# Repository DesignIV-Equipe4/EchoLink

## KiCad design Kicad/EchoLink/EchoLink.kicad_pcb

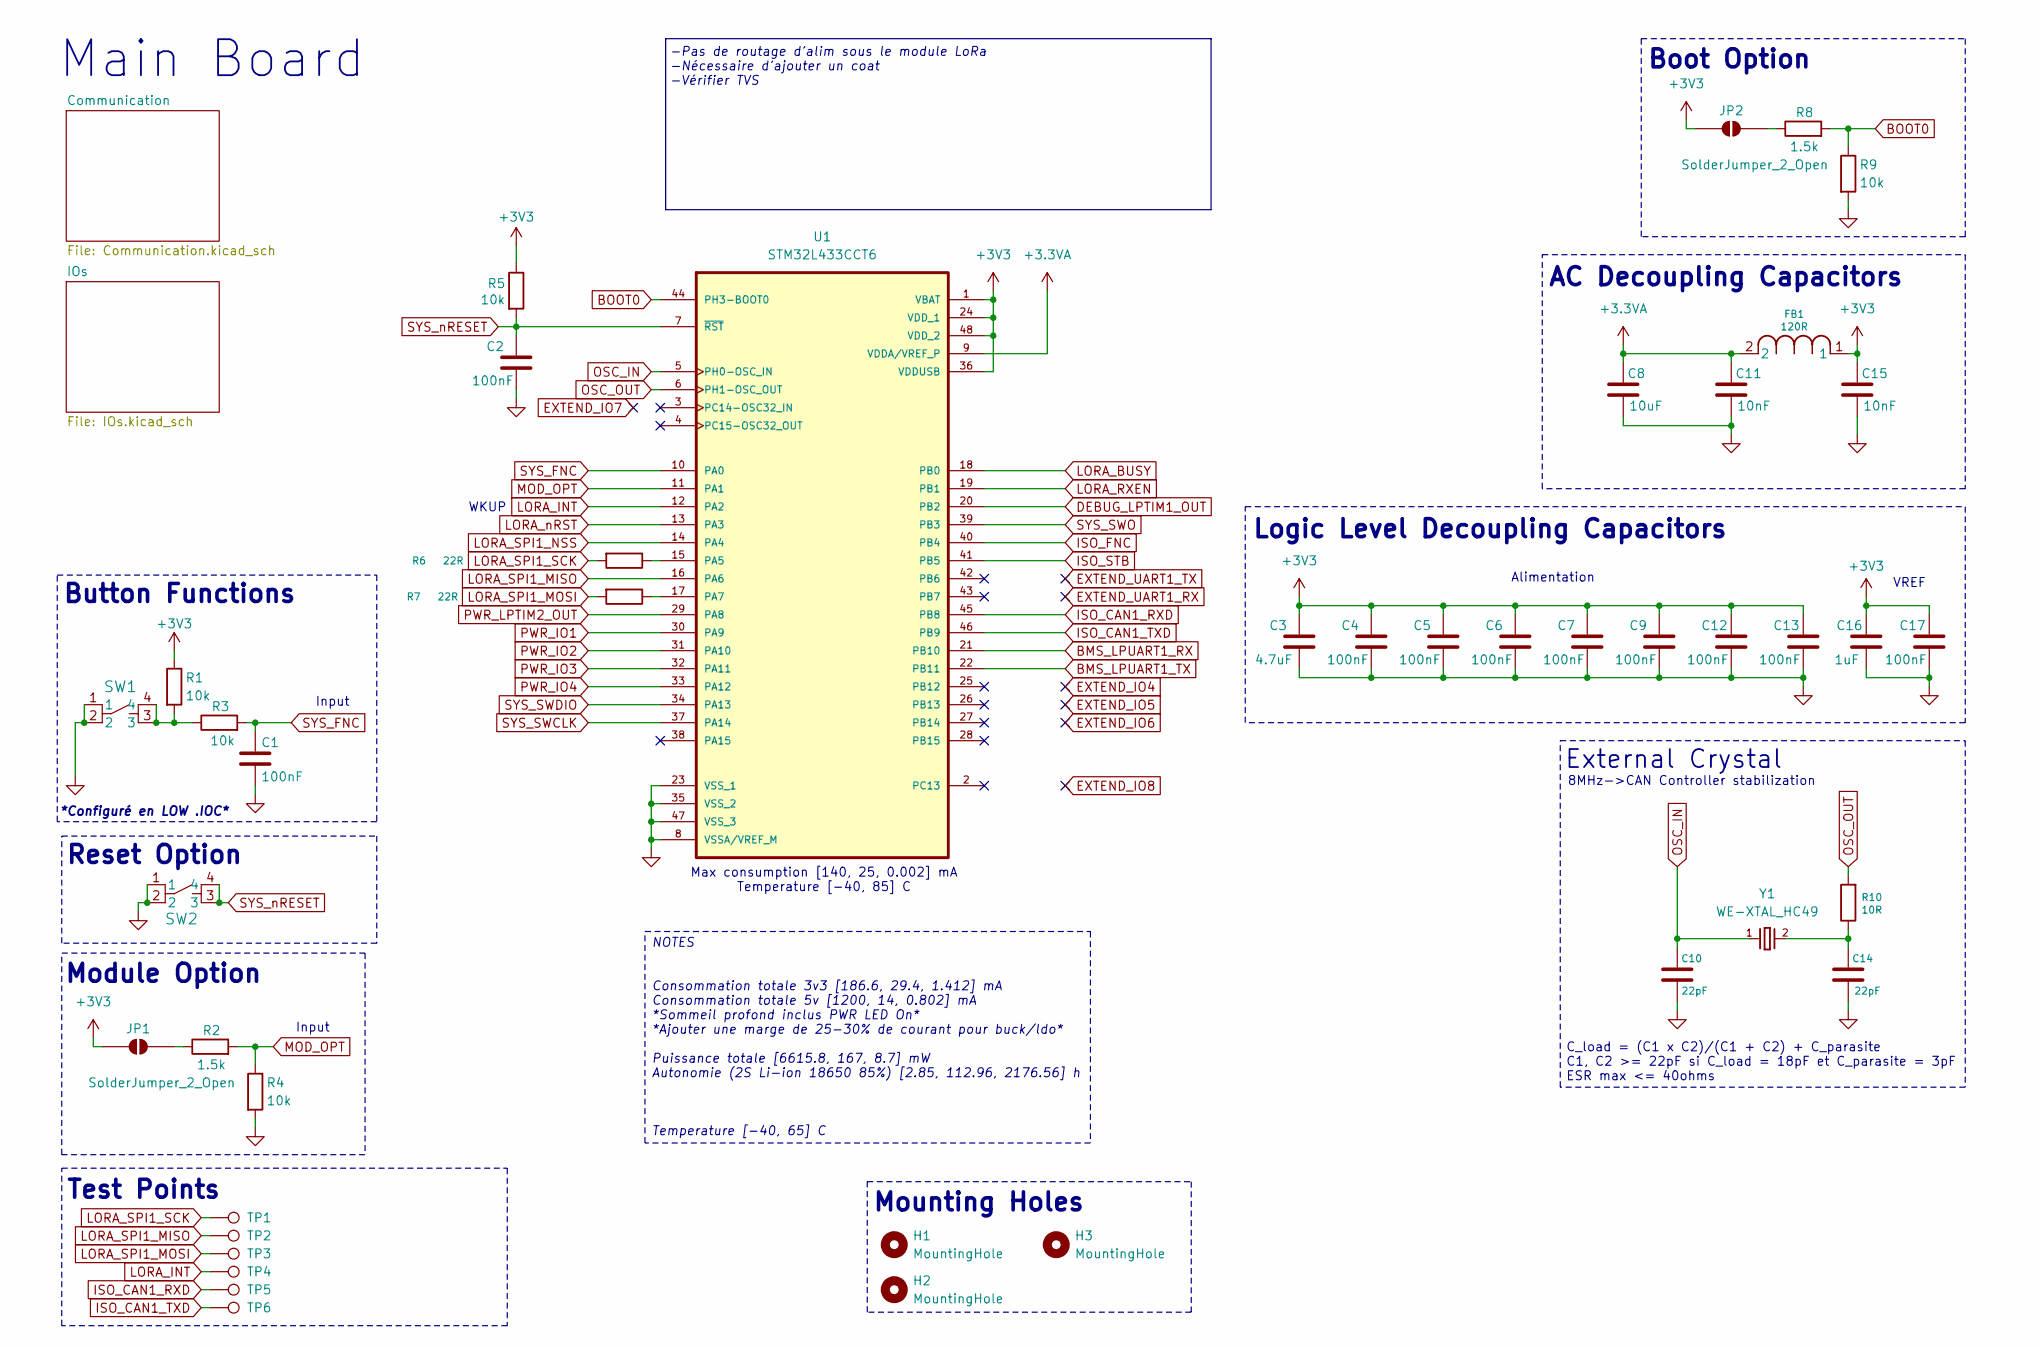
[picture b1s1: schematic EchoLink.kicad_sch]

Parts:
C1, C2, C4, C5, C6, C7, C9, C12, C13, C17: 100nF; C_0603_1608Metric; Manufacturer_Part_Number C0603C104K5RACTU; DigiKey_Part_Number 311-3342-1-ND
C3: 4.7uF; C_0603_1608Metric; Manufacturer_Part_Number GRM188R61E475KE11D; DigiKey_Part_Number 311-3342-1-ND
C8: 10uF; C_0603_1608Metric; Manufacturer_Part_Number LMK107BBJ106MALT; DigiKey_Part_Number 4713-GMC10X5R106M35NTTR-ND
C10, C14: 22pF; C_0402_1005Metric; Manufacturer_Part_Number QSCT251Q220F1GV001E; DigiKey_Part_Number 712-QSCT251Q220F1GV001ECT-ND
C11, C15: 10nF; C_0402_1005Metric; Manufacturer_Part_Number GRM155R71C103KA01D; DigiKey_Part_Number 490-1313-1-ND
C16: 1uF; C_0603_1608Metric; Manufacturer_Part_Number C0603C105K4RACTU; DigiKey_Part_Number 311-3342-1-ND
FB1: 120R; R_0805_2012Metric; Manufacturer_Part_Number 2508051217Y6; DigiKey_Part_Number 1934-1472-1-ND
H1, H2, H3: MountingHole; MountingHole_2.2mm_M2_Pad_Via
JP1, JP2: SolderJumper_2_Open; SolderJumper-2_P1.3mm_Open_RoundedPad1.0x1.5mm
R1, R4, R5, R9: 10k; R_0603_1608Metric; Manufacturer_Part_Number RC0603FR-0710KL; DigiKey_Part_Number 311-10.0KHRCT-ND
R2, R8: 1.5k; R_0603_1608Metric; Manufacturer_Part_Number ERA-3AEB152V; DigiKey_Part_Number P1.5KDBCT-ND
R3: 10k; R_0603_1608Metric; Manufacturer_Part_Number RC0603FR-0710KL; DigiKey_Part_Number P1.5KDBCT-ND
R6, R7: 22R; C_0603_1608Metric; Manufacturer_Part_Number RMCF0603FT22R0; DigiKey_Part_Number YAG3460CT-ND
R10: 10R; R_0603_1608Metric; Manufacturer_Part_Number RC0805FR-0710RL; DigiKey_Part_Number 311-10.0CRCT-ND
SW1, SW2: PTS526 SM15 SMTR2 LFS; SON4_PTS526 SM15 SMTR2 LFS_CNK; Manufacturer_Part_Number PTS526SM15SMTR2 LFS; DigitKey_Part_Number CKN12220-1-ND
TP1, TP2, TP3, TP4, TP5, TP6: TestPoint; TestPoint_Pad_D1.0mm
U1: STM32L433CCT6; QFP50P900X900X160-48N; Manufacturer_Part_Number STM32L433CCT6; DigiKey_Part_Number 497-16579-ND
Y1: WE-XTAL_HC49; Manufacturer_Part_Number 830050510; DigiKey_Part_Number 1923-830050510CT-ND

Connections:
+3.3VA: C8.1, C11.1, FB1.2, U1.9 (VDDA/VREF_P)
+3V3: C3.1, C4.1, C5.1, C6.1, C7.1, C9.1, C12.1, C13.1, C15.1, C16.1, C17.1, FB1.1, JP1.1 (A), JP2.1 (A), R1.1, R5.1, U1.1 (VBAT), U1.24 (VDD_1), U1.36 (VDDUSB), U1.48 (VDD_2); also elsewhere on the board
BMS_LPUART1_RX: U1.21 (PB10); also elsewhere on the board
BMS_LPUART1_TX: U1.22 (PB11); also elsewhere on the board
BOOT0: R8.2, R9.1, U1.44 (PH3-BOOT0)
DEBUG_LPTIM1_OUT: U1.20 (PB2); also elsewhere on the board
GND: C1.2, C2.2, C3.2, C4.2, C5.2, C6.2, C7.2, C8.2, C9.2, C10.1, C11.2, C12.2, C13.2, C14.1, C15.2, C16.2, C17.2, R4.2, R9.2, SW1.1, SW1.2, SW2.1, SW2.2, U1.8 (VSSA/VREF_M), U1.23 (VSS_1), U1.35 (VSS_2), U1.47 (VSS_3); also elsewhere on the board
ISO_CAN1_RXD: TP5.1 (1_1), U1.45 (PB8); also elsewhere on the board
ISO_CAN1_TXD: TP6.1 (1_1), U1.46 (PB9); also elsewhere on the board
ISO_FNC: U1.40 (PB4); also elsewhere on the board
ISO_STB: U1.41 (PB5); also elsewhere on the board
LORA_BUSY: U1.18 (PB0); also elsewhere on the board
LORA_INT: TP4.1 (1_1), U1.12 (PA2); also elsewhere on the board
LORA_RXEN: U1.19 (PB1); also elsewhere on the board
LORA_SPI1_MISO: TP2.1 (1_1), U1.16 (PA6); also elsewhere on the board
LORA_SPI1_MOSI: R7.2, TP3.1 (1_1); also elsewhere on the board
LORA_SPI1_NSS: U1.14 (PA4); also elsewhere on the board
LORA_SPI1_SCK: R6.2, TP1.1 (1_1); also elsewhere on the board
LORA_nRST: U1.13 (PA3); also elsewhere on the board
MOD_OPT: R2.2, R4.1, U1.11 (PA1)
unnamed: C14.2, R10.1, Y1.2
unnamed: JP1.2 (B), R2.1
unnamed: JP2.2 (B), R8.1
unnamed: R1.2, R3.1, SW1.3, SW1.4
unnamed: R6.1, U1.15 (PA5)
unnamed: R7.1, U1.17 (PA7)
OSC_IN: C10.2, U1.5 (PH0-OSC_IN), Y1.1
OSC_OUT: R10.2, U1.6 (PH1-OSC_OUT)
PWR_IO1: U1.30 (PA9); also elsewhere on the board
PWR_IO2: U1.31 (PA10); also elsewhere on the board
PWR_IO3: U1.32 (PA11); also elsewhere on the board
PWR_IO4: U1.33 (PA12); also elsewhere on the board
PWR_LPTIM2_OUT: U1.29 (PA8); also elsewhere on the board
SYS_FNC: C1.1, R3.2, U1.10 (PA0)
SYS_SWCLK: U1.37 (PA14); also elsewhere on the board
SYS_SWDIO: U1.34 (PA13); also elsewhere on the board
SYS_SWO: U1.39 (PB3); also elsewhere on the board
SYS_nRESET: C2.1, R5.2, SW2.3, SW2.4, U1.7 (~RST); also elsewhere on the board

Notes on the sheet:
Module Option
8MHz->CAN Controller stabilization
*Configuré en LOW .IOC*
WKUP
External Crystal
Main Board
AC Decoupling Capacitors
Logic Level Decoupling Capacitors
Boot Option
Input
C_load = (C1 x C2)/(C1 + C2) + C_parasite C1, C2 >= 22pF si C_load = 18pF et C_parasite = 3pF ESR max <= 40ohms
VREF
Reset Option
-Pas de routage d'alim sous le module LoRa -Nécessaire d'ajouter un coat -Vérifier TVS
Test Points
Alimentation
Max consumption [140, 25, 0.002] mA Temperature [-40, 85] C
NOTES Consommation totale 3v3 [186.6, 29.4, 1.412] mA Consommation totale 5v [1200, 14, 0.802] mA *Sommeil profond inclus PWR LED On* *Ajouter une marge de 25-30% de courant pour buck/ldo* Puissance totale [6615.8, 167, 8.7] mW Autonomie (2S Li-ion 18650 85%) [2.85, 112.96, 2176.56] h Temperature [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
Mounting Holes
Button Functions

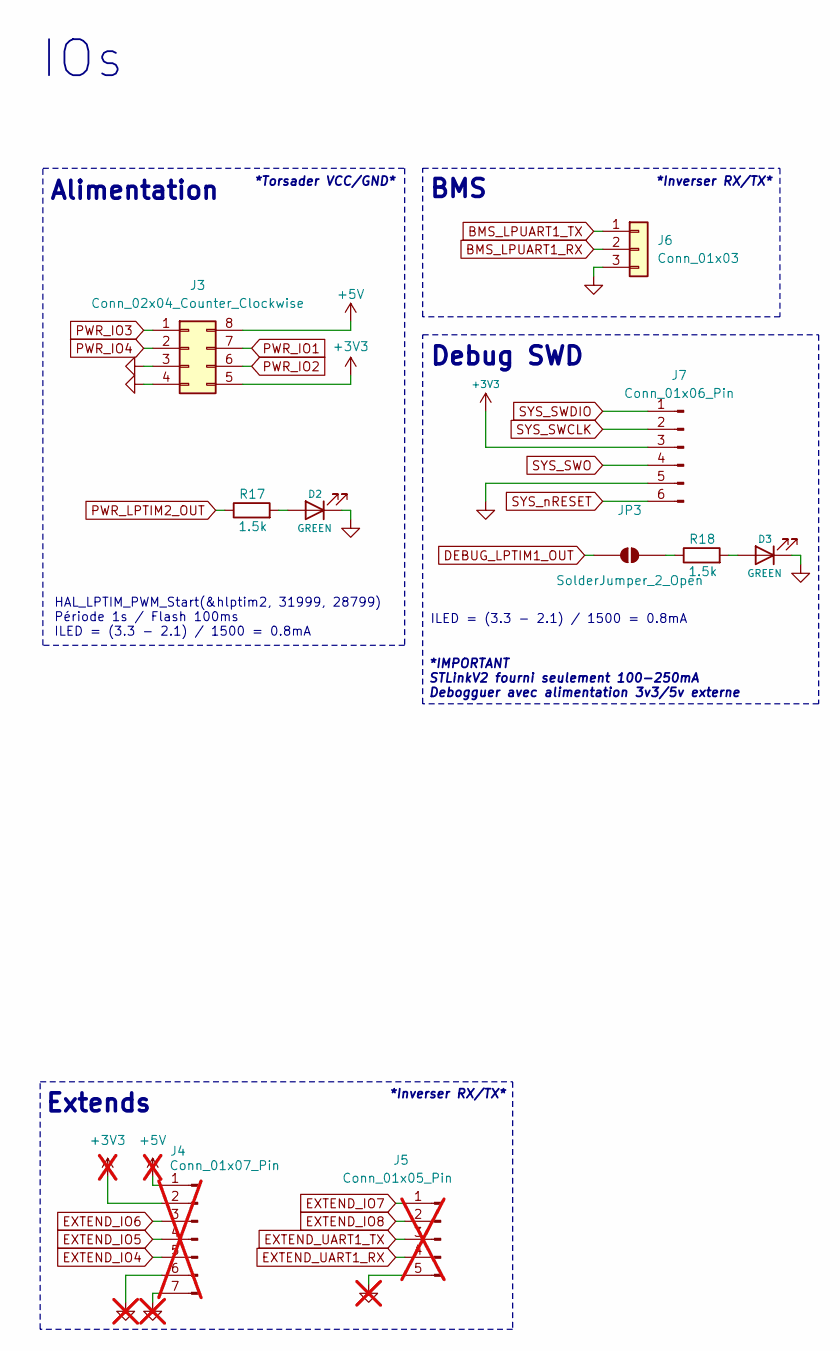
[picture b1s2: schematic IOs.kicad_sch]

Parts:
D2, D3: GREEN; R_0603_1608Metric; Manufacturer_Part_Number QBLP601-AG15; DigiKey_Part_Number 1516-QBLP601-AG15CT-ND
J3: Conn_02x04_Counter_Clockwise; CONN_SD-43045-008_08_MOL; Manufacturer_Part_Number 0430450821; DigitKey_Part_Number WM2675-ND
J4: Conn_01x07_Pin; PinHeader_1x07_P2.54mm_Vertical; not fitted
J5: Conn_01x05_Pin; PinHeader_1x05_P2.54mm_Vertical; not fitted
J6: Conn_01x03; CONN_SD-43650-002_03_MOL; Manufacturer_Part_Number 0436500303; DigitKey_Part_Number 23-0436500303-ND
J7: Conn_01x06_Pin; PinHeader_1x06_P2.54mm_Vertical
JP3: SolderJumper_2_Open; SolderJumper-2_P1.3mm_Open_RoundedPad1.0x1.5mm
R17, R18: 1.5k; R_0603_1608Metric; Manufacturer_Part_Number ERA-3AEB152V; DigiKey_Part_Number P1.5KDBCT-ND

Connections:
+3V3: J3.5, J4.2, J7.3; also elsewhere on the board
+5V: J3.8, J4.1; also elsewhere on the board
BMS_LPUART1_RX: J6.2; also elsewhere on the board
BMS_LPUART1_TX: J6.1; also elsewhere on the board
DEBUG_LPTIM1_OUT: JP3.1 (A); also elsewhere on the board
GND: D2.1 (K), D3.1 (K), J3.3, J3.4, J4.6, J4.7, J5.5, J6.3, J7.5; also elsewhere on the board
unnamed: D2.2 (A), R17.2
unnamed: D3.2 (A), R18.2
unnamed: JP3.2 (B), R18.1
PWR_IO1: J3.7; also elsewhere on the board
PWR_IO2: J3.6; also elsewhere on the board
PWR_IO3: J3.1; also elsewhere on the board
PWR_IO4: J3.2; also elsewhere on the board
PWR_LPTIM2_OUT: R17.1; also elsewhere on the board
SYS_SWCLK: J7.2; also elsewhere on the board
SYS_SWDIO: J7.1; also elsewhere on the board
SYS_SWO: J7.4; also elsewhere on the board
SYS_nRESET: J7.6; also elsewhere on the board

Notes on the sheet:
IOs
BMS
Extends
*Inverser RX/TX*
*IMPORTANT STLinkV2 fourni seulement 100-250mA Debogguer avec alimentation 3v3/5v externe
HAL_LPTIM_PWM_Start(&hlptim2, 31999, 28799) Période 1s / Flash 100ms ILED = (3.3 - 2.1) / 1500 = 0.8mA
Debug SWD
Alimentation
*Torsader VCC/GND*
ILED = (3.3 - 2.1) / 1500 = 0.8mA

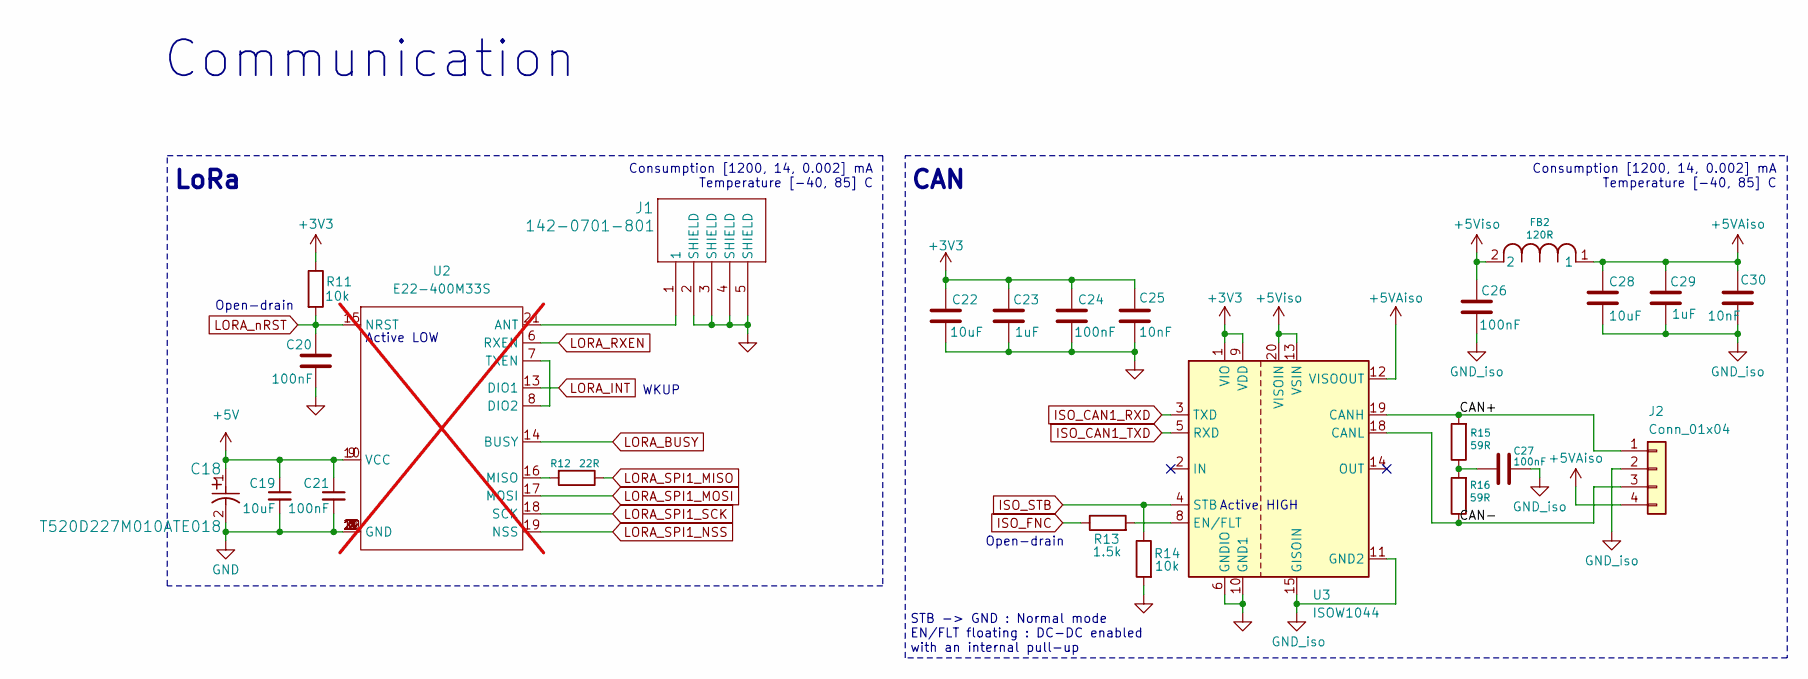
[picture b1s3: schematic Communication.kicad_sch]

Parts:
C18: T520D227M010ATE018; CAPMP7.6X4.3_3.1N_KEM; Manufacturer_Part_Number T520D227M010ATE018; DigitKey_Part_Number 399-4045-1-ND
C19: 10uF; C_0603_1608Metric; Manufacturer_Part_Number LMK107BBJ106MALT; DigitKey_Part_Number 587-3258-1-ND
C20: 100nF; C_0603_1608Metric; Manufacturer_Part_Number C0603C104K5RACTU; DigiKey_Part_Number 311-3342-1-ND
C21: 100nF; C_0603_1608Metric; Manufacturer_Part_Number C0603C104K5RACTU; DigitKey_Part_Number 399-C0603C104K5RACTUCT-ND
C22, C28: 10uF; C_0603_1608Metric; Manufacturer_Part_Number LMK107BBJ106MALT; DigiKey_Part_Number 1276-2891-1-ND
C23, C29: 1uF; C_0603_1608Metric; Manufacturer_Part_Number C0603C105K4RACTU; DigiKey_Part_Number 1276-1029-1-ND
C24, C26, C27: 100nF; C_0603_1608Metric; Manufacturer_Part_Number C0603C104K5RACTU; DigiKey_Part_Number 399-C0603C104K3RACTUCT-ND
C25, C30: 10nF; C_0603_1608Metric; Manufacturer_Part_Number CC0603KRX7R9BB103; DigiKey_Part_Number 1276-2434-1-ND
FB2: 120R; R_0805_2012Metric; Manufacturer_Part_Number 2508051217Y6; DigiKey_Part_Number 1934-1472-1-ND
J1: 142-0701-801; CONN_142-0701-801; Manufacturer_Part_Number 142-0701-801; DigitKey_Part_Number J502-ND
J2: Conn_01x04; CONN_SD-43045-008_04_MOL; Manufacturer_Part_Number 0430450423; DigitKey_Part_Number WM7485-ND
R11, R14: 10k; R_0603_1608Metric; Manufacturer_Part_Number RC0603FR-0710KL; DigiKey_Part_Number 311-10.0KHRCT-ND
R12: 22R; C_0603_1608Metric; Manufacturer_Part_Number RMCF0603FT22R0; DigiKey_Part_Number YAG3460CT-ND
R13: 1.5k; R_0603_1608Metric; Manufacturer_Part_Number ERA-3AEB152V; DigiKey_Part_Number P1.5KDBCT-ND
R15, R16: 59R; R_0603_1608Metric; Manufacturer_Part_Number RK73H1JTTD59R0F; DigiKey_Part_Number 311-59.0CRCT-ND
U2: E22-400M33S; not fitted
U3: ISOW1044; ISOW1044BDFMR; Manufacturer_Part_Number ISOW1044BDFMR; DigiKey_Part_Number 296-ISOW1044BDFMRCT-ND

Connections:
+3V3: C22.1, C23.1, C24.1, C25.1, R11.1, U3.1 (VIO), U3.9 (VDD); also elsewhere on the board
+5V: C18.1, C19.1, C21.1, U2.9 (VCC), U2.10 (VCC); also elsewhere on the board
+5VAiso: C28.1, C29.1, C30.1, FB2.1, J2.4, U3.12 (VISOOUT); also elsewhere on the board
+5Viso: C26.1, FB2.2, U3.13 (VSIN), U3.20 (VISOIN)
/Communication/CAN+: J2.1, R15.2, U3.19 (CANH)
/Communication/CAN-: J2.3, R16.1, U3.18 (CANL)
GND: C18.2, C19.2, C20.2, C21.2, C22.2, C23.2, C24.2, C25.2, J1.2 (SHIELD), J1.3 (SHIELD), J1.4 (SHIELD), J1.5 (SHIELD), R14.2, U2.0 (GND), U2.1 (GND), U2.2 (GND), U2.3 (GND), U2.4 (GND), U2.5 (GND), U2.11 (GND), U2.12 (GND), U2.20 (GND), U2.22 (GND), U3.6 (GNDIO), U3.10 (GND1); also elsewhere on the board
GND_iso: C26.2, C27.2, C28.2, C29.2, C30.2, J2.2, U3.11 (GND2), U3.15 (GISOIN), U3.16 (GISOIN), U3.17 (GISOIN); also elsewhere on the board
ISO_CAN1_RXD: U3.3 (TXD); also elsewhere on the board
ISO_CAN1_TXD: U3.5 (RXD); also elsewhere on the board
ISO_FNC: R13.1; also elsewhere on the board
ISO_STB: R14.1, U3.4 (STB); also elsewhere on the board
LORA_BUSY: U2.14 (BUSY); also elsewhere on the board
LORA_INT: U2.13 (DIO1); also elsewhere on the board
LORA_RXEN: U2.6 (RXEN); also elsewhere on the board
LORA_SPI1_MISO: R12.1; also elsewhere on the board
LORA_SPI1_MOSI: U2.17 (MOSI); also elsewhere on the board
LORA_SPI1_NSS: U2.19 (NSS); also elsewhere on the board
LORA_SPI1_SCK: U2.18 (SCK); also elsewhere on the board
LORA_nRST: C20.1, R11.2, U2.15 (NRST); also elsewhere on the board
unnamed: C27.1, R15.1, R16.2
unnamed: J1.1, U2.21 (ANT)
unnamed: U2.7 (TXEN), U2.8 (DIO2)
unnamed: R12.2, U2.16 (MISO)
unnamed: R13.2, U3.8 (EN/FLT)

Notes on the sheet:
WKUP
Active HIGH
Open-drain
Consumption [1200, 14, 0.002] mA Temperature [-40, 85] C
Communication
STB -> GND : Normal mode EN/FLT floating : DC-DC enabled with an internal pull-up
LoRa
Active LOW
CAN

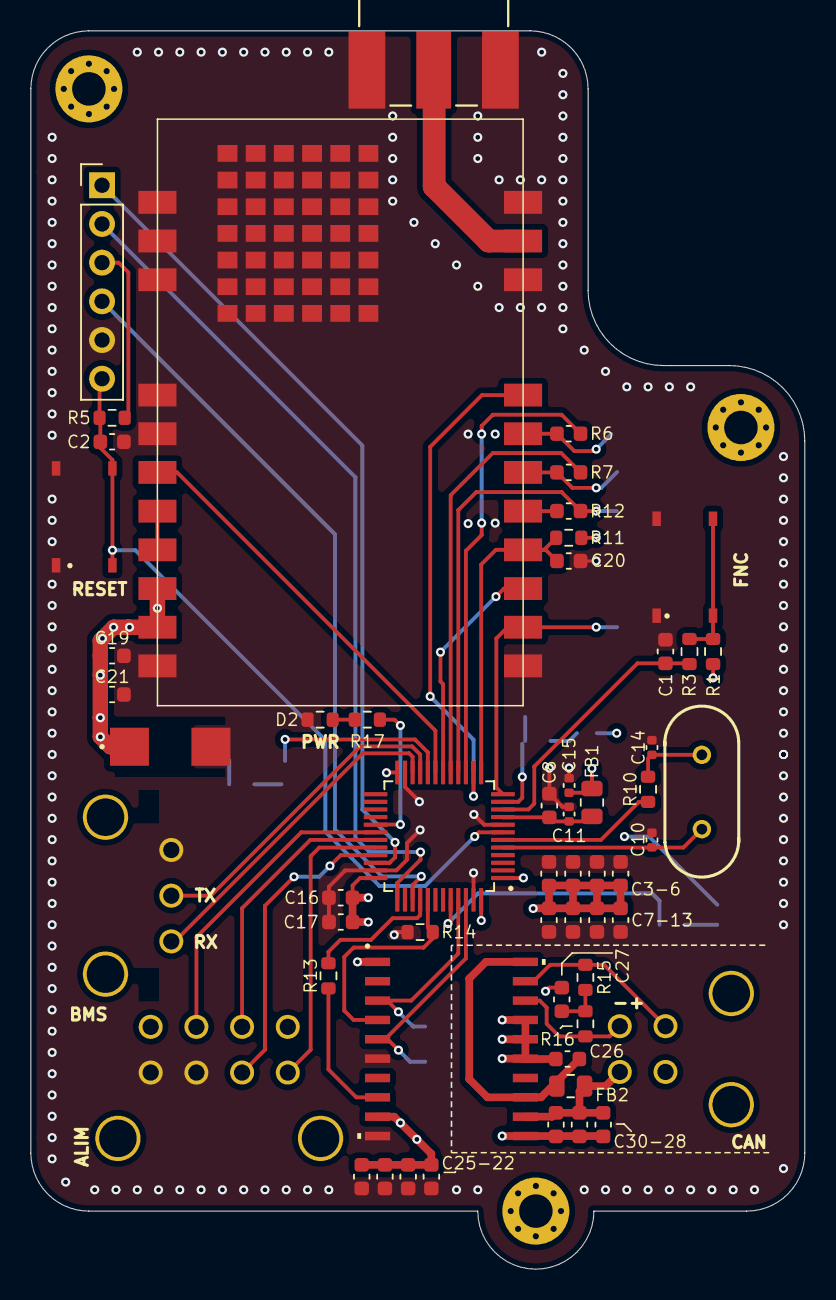
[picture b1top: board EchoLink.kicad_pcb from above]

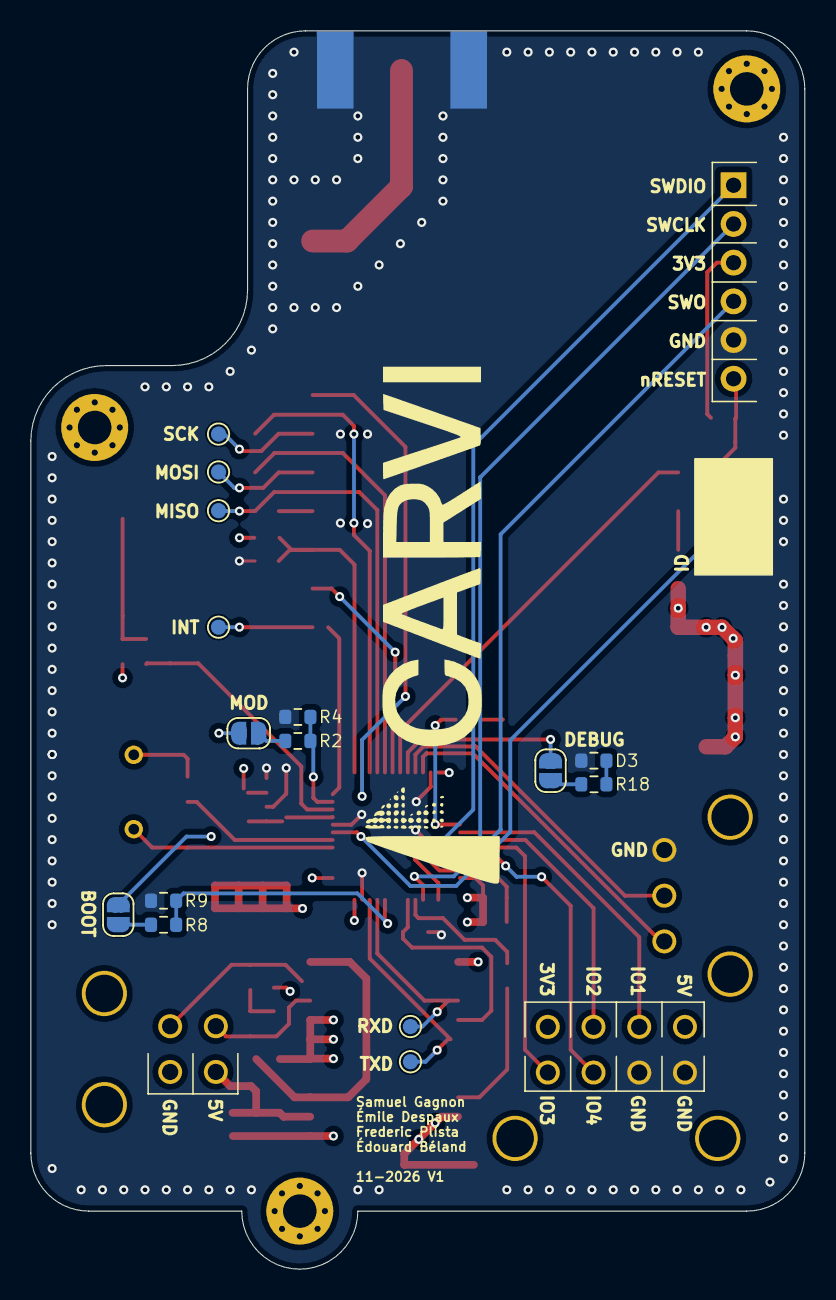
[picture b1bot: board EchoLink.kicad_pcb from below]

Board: 4 copper layers, 50.8 x 81.3 mm, 76 parts (16 on the bottom side), 52 nets.

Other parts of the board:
C3-6: 4.7uF; C_0603_1608Metric
C7-13: 100nF; C_0603_1608Metric
C25-22, C30-28: 10uF; C_0603_1608Metric
G1: LOGO; Carvi

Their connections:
+3V3: C3-6.1, C7-13.1, C25-22.1; also elsewhere on the board
+5VAiso: C30-28.1; also elsewhere on the board
GND: C3-6.2, C7-13.2, C25-22.2; also elsewhere on the board
GND_iso: C30-28.2; also elsewhere on the board

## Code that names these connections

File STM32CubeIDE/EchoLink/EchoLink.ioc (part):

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Mcu.Name=STM32L433C(B-C)Tx
Mcu.Package=LQFP48
Mcu.UserName=STM32L433CCTx
PA0.GPIOParameters=GPIO_Label
PA0.GPIO_Label=SYS_FNC
PA0.Mode=SYS_WakeUp0
PA0.Signal=SYS_WKUP1
PA1.GPIOParameters=GPIO_Label
PA1.GPIO_Label=MOD_OPT
PA1.Signal=GPIO_Input
PA10.GPIOParameters=GPIO_Label
PA10.GPIO_Label=PWR_IO2
PA10.Signal=GPIO_Output
PA11.GPIOParameters=GPIO_Label
PA11.GPIO_Label=PWR_IO3
PA11.Signal=GPIO_Output
PA12.GPIOParameters=GPIO_Label
PA12.GPIO_Label=PWR_IO4
PA12.Signal=GPIO_Output
PA13\ (JTMS-SWDIO).GPIOParameters=GPIO_Label
PA13\ (JTMS-SWDIO).GPIO_Label=SYS_SWDIO
PA13\ (JTMS-SWDIO).Mode=Trace_Asynchronous_SW
PA13\ (JTMS-SWDIO).Signal=SYS_JTMS-SWDIO
PA14\ (JTCK-SWCLK).GPIOParameters=GPIO_Label
PA14\ (JTCK-SWCLK).GPIO_Label=SYS_SWCLK
PA14\ (JTCK-SWCLK).Mode=Trace_Asynchronous_SW
PA14\ (JTCK-SWCLK).Signal=SYS_JTCK-SWCLK
PA2.GPIOParameters=GPIO_Label
PA2.GPIO_Label=LORA_INT
PA2.Mode=SYS_WakeUp3
PA2.Signal=SYS_WKUP4
PA3.GPIOParameters=PinState,GPIO_PuPd,GPIO_Label,GPIO_ModeDefaultOutputPP
PA3.GPIO_Label=LORA_nRST
PA3.GPIO_ModeDefaultOutputPP=GPIO_MODE_OUTPUT_OD
PA3.GPIO_PuPd=GPIO_NOPULL
PA3.PinState=GPIO_PIN_SET
PA3.Signal=GPIO_Output
PA4.GPIOParameters=PinState,GPIO_Label
PA4.GPIO_Label=LORA_SPI1_NSS
PA4.PinState=GPIO_PIN_SET
PA4.Signal=GPIO_Output
PA5.GPIOParameters=GPIO_Label
PA5.GPIO_Label=LORA_SPI1_SCK
PA5.Mode=Full_Duplex_Master
PA5.Signal=SPI1_SCK
PA6.GPIOParameters=GPIO_Label
PA6.GPIO_Label=LORA_SPI1_MISO
PA6.Mode=Full_Duplex_Master
PA6.Signal=SPI1_MISO
PA7.GPIOParameters=GPIO_Label
PA7.GPIO_Label=LORA_SPI1_MOSI
PA7.Mode=Full_Duplex_Master
PA7.Signal=SPI1_MOSI
PA8.GPIOParameters=GPIO_Label
PA8.GPIO_Label=PWR_LPTIM2_OUT
PA8.Mode=WaveformGeneration
PA8.Signal=LPTIM2_OUT
PA9.GPIOParameters=GPIO_Label
PA9.GPIO_Label=PWR_IO1
PA9.Signal=GPIO_Output
PB0.GPIOParameters=GPIO_Label
PB0.GPIO_Label=LORA_BUSY
PB0.Signal=GPIO_Input
PB1.GPIOParameters=GPIO_Label
PB1.GPIO_Label=LORA_RXEN
PB1.Signal=GPIO_Output
PB10.GPIOParameters=GPIO_Label
PB10.GPIO_Label=BMS_LPUART1_RX
PB10.Mode=Asynchronous
PB10.Signal=LPUART1_RX
PB11.GPIOParameters=GPIO_Label
PB11.GPIO_Label=BMS_LPUART1_TX
PB11.Mode=Asynchronous
PB11.Signal=LPUART1_TX
PB2.GPIOParameters=GPIO_Label
PB2.GPIO_Label=DEBUG_LPTIM1_OUT
PB2.Mode=WaveformGeneration
PB2.Signal=LPTIM1_OUT
PB3\ (JTDO-TRACESWO).GPIOParameters=GPIO_Label
PB3\ (JTDO-TRACESWO).GPIO_Label=SYS_SWO
PB3\ (JTDO-TRACESWO).Mode=Trace_Asynchronous_SW
PB3\ (JTDO-TRACESWO).Signal=SYS_JTDO-SWO
PB4\ (NJTRST).GPIOParameters=GPIO_PuPd,GPIO_Label,GPIO_ModeDefaultOutputPP
PB4\ (NJTRST).GPIO_Label=ISO_FNC
PB4\ (NJTRST).GPIO_ModeDefaultOutputPP=GPIO_MODE_OUTPUT_OD
PB4\ (NJTRST).GPIO_PuPd=GPIO_NOPULL
PB4\ (NJTRST).Signal=GPIO_Output
PB5.GPIOParameters=GPIO_Label
PB5.GPIO_Label=ISO_STB
PB5.Signal=GPIO_Output
PB8.GPIOParameters=GPIO_Label
PB8.GPIO_Label=ISO_CAN1_RXD
PB8.Mode=CAN_Activate
PB8.Signal=CAN1_RX
PB9.GPIOParameters=GPIO_Label
PB9.GPIO_Label=ISO_CAN1_TXD
PB9.Mode=CAN_Activate
PB9.Signal=CAN1_TX
PH0-OSC_IN\ (PH0).GPIOParameters=GPIO_Label
PH0-OSC_IN\ (PH0).GPIO_Label=OSC_IN
PH0-OSC_IN\ (PH0).Mode=HSE-External-Oscillator
PH0-OSC_IN\ (PH0).Signal=RCC_OSC_IN
PH1-OSC_OUT\ (PH1).GPIOParameters=GPIO_Label
PH1-OSC_OUT\ (PH1).GPIO_Label=OSC_OUT
PH1-OSC_OUT\ (PH1).Mode=HSE-External-Oscillator
PH1-OSC_OUT\ (PH1).Signal=RCC_OSC_OUT
RCC.HSE_VALUE=8000000
RCC.SYSCLKFreq_VALUE=80000000
RCC.SYSCLKSource=RCC_SYSCLKSOURCE_PLLCLK
board=custom
